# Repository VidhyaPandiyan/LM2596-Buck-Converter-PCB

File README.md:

# LM2596-Buck-Converter-PCB
12V to 5V Buck Converter PCB designed in KiCad

## Overview

A compact 12V to 5V DC-DC buck converter designed using KiCad and based on the LM2596S-5.0 switching regulator.

## Features

* 12V DC Input
* Regulated 5V Output
* LM2596S-5.0 Switching Regulator
* Reverse Polarity Protection
* Power Indicator LED
* Input and Output Filtering Capacitors
* Designed in KiCad

## Applications

* ESP32 Projects
* Arduino Projects
* IoT Devices
* Sensor Nodes
* Embedded Systems

## Tools Used

* KiCad
* PCB Editor
* KiCad 3D Viewer

## Author

Vidhya Pandiyan
Embedded Engineer

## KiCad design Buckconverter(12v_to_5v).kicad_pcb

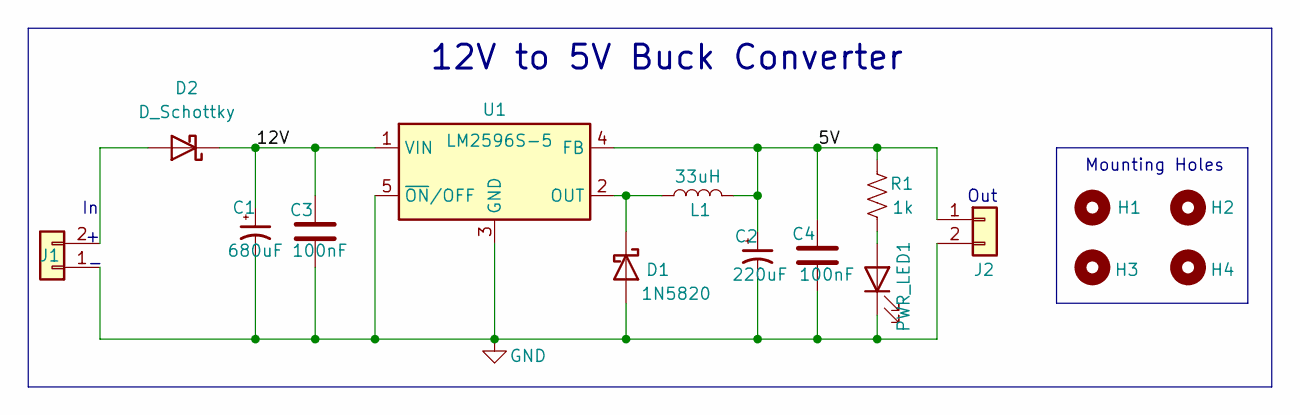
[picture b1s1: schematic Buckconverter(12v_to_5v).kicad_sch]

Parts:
C1: 680uF; CP_Radial_D12.5mm_P5.00mm
C2: 220uF; CP_Radial_D4.0mm_P1.50mm
C3: 100nF; C_0805_2012Metric
C4: 100nF; C_0805_2012Metric_Pad1.18x1.45mm_HandSolder
D1: 1N5820; D_DO-201AD_P5.08mm_Vertical_AnodeUp
D2: D_Schottky; D_0805_2012Metric_Pad1.15x1.40mm_HandSolder
H1, H2, H3, H4: MountingHole; MountingHole_2.1mm
J1, J2: Conn_01x02; PinHeader_1x02_P2.00mm_Vertical
L1: 33uH; L_12x12mm_H8mm
PWR_LED1: LED; LED_0603_1608Metric
R1: 1k; R_0603_1608Metric
U1: LM2596S-5; TO-263-5_TabPin3

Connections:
/5V: C2.1, C4.1, J2.1, L1.2, R1.1, U1.4 (FB)
/12V: C1.1, C3.1, D2.1 (K), U1.1 (VIN)
GND: C1.2, C2.2, C3.2, C4.2, D1.2 (A), J1.1, J2.2, PWR_LED1.1 (K), U1.3 (GND), U1.5 (~ON/OFF)
unnamed: D1.1 (K), L1.1, U1.2 (OUT)
unnamed: D2.2 (A), J1.2
unnamed: PWR_LED1.2 (A), R1.2

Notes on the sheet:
Out
Mounting Holes
12V to 5V Buck Converter

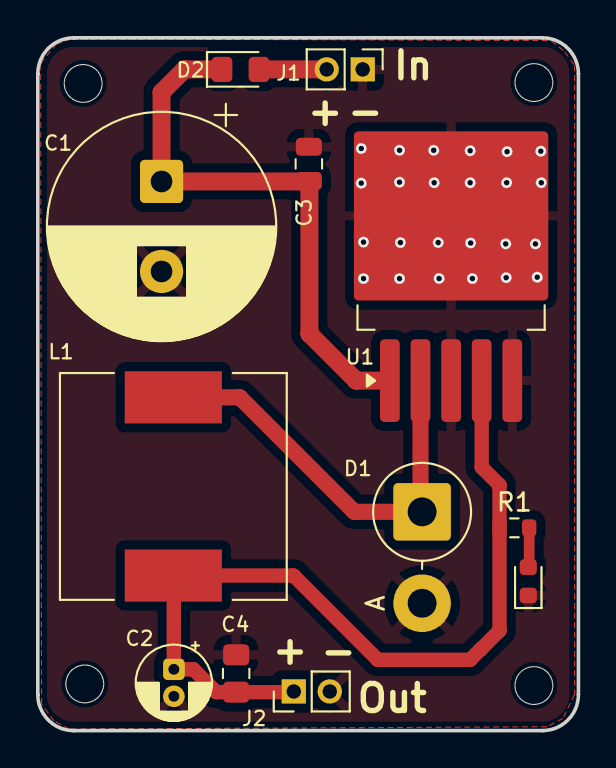
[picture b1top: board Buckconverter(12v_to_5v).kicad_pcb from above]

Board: 2 copper layers, 30.0 x 38.5 mm, 16 parts (0 on the bottom side), 6 nets.

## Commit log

2026-06-11 Enhance README with project details and author info
    Added detailed overview, features, applications, tools, and author information to the README.
2026-06-11 LM2596 buck converter project files
2026-06-11 project images
